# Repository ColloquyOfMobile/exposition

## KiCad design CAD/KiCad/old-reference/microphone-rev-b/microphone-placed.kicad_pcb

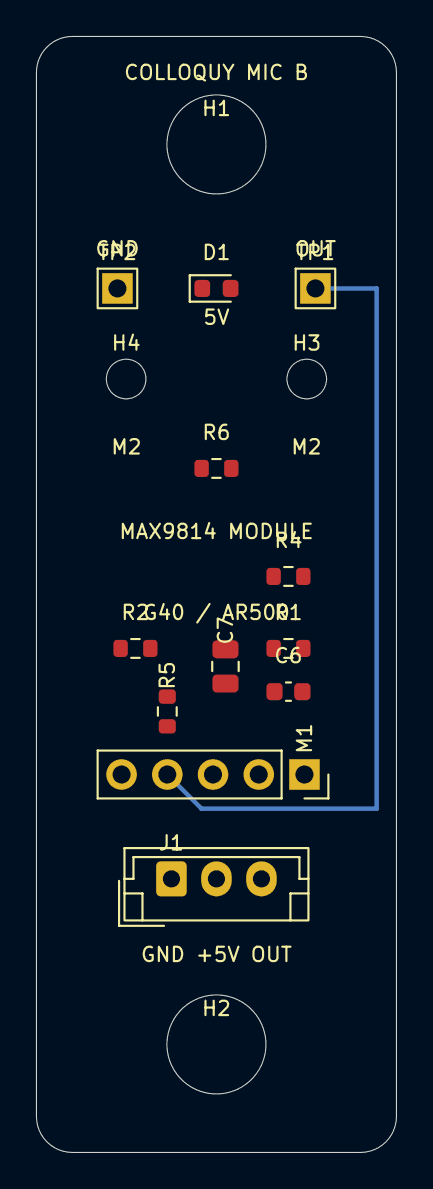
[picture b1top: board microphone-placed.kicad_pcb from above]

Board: 2 copper layers, 20.0 x 62.0 mm, 16 parts (0 on the bottom side), 8 nets.

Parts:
C6: 100nF; C_0603_1608Metric
C7: 22uF X5R 10V; C_0805_2012Metric
D1: GREEN LED; LED_0603_1608Metric
H1, H2: M5 / 12mm copper keepout; MountingHole_5.5mm_Keepout12
H3, H4: M2 MODULE / INSULATING SPACER; MountingHole_2.2mm_M2_Keepout6
J1: GND / +5V / OUT; JST_EH_B3B-EH-A_1x03_P2.50mm_Vertical
M1: MAX9814 MODULE / 1x05 SOCKET; MAX9814_Module_Socket_1x05
R1: 0R / GAIN VDD 40dB; R_0603_1608Metric
R2: 0R / AR GND 1:500; R_0603_1608Metric
R4: 33R; R_0603_1608Metric
R5: 470R; R_0603_1608Metric
R6: 2K2; R_0603_1608Metric
TP1: MICOUT; TestPin_1x01_P2.54mm
TP2: GND; TestPin_1x01_P2.54mm

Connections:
+5V: J1.2, R4.1, R6.1
AR: M1.5, R2.1
GAIN: M1.3, R1.1
GND: C6.2, C7.2, D1.1, J1.1, M1.1, R2.2, TP2.1
MICOUT: M1.4, R5.1, TP1.1
OUT: J1.3, R5.2
VDD: C6.1, C7.1, M1.2, R1.2, R4.2
led/D1: D1.2, R6.2

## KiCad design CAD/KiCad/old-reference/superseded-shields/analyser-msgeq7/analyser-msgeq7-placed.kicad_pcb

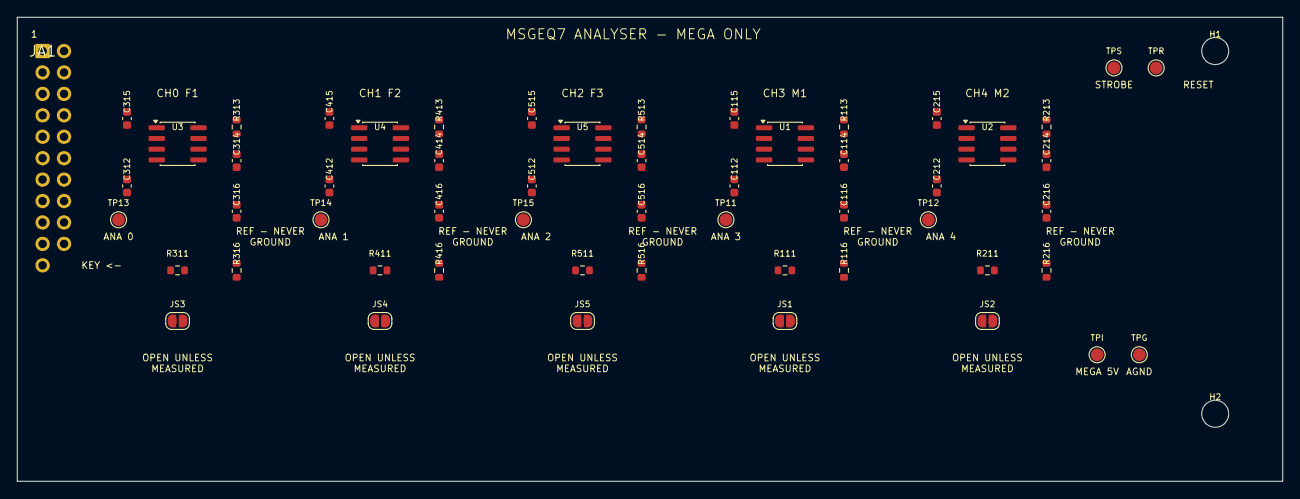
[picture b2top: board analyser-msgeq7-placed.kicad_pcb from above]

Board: 2 copper layers, 150.0 x 55.0 mm, 57 parts (1 on the bottom side), 34 nets, no tracks yet.

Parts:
C112, C115, C116, C212, C215, C216, C312, C315, C316, C412, C415, C416, C512, C515, C516: 100nF; C_0603_1608Metric
C114, C214, C314, C414, C514: 33pF C0G; C_0603_1608Metric
H1, H2: M3 retention; MountingHole_3.2mm_M3
JA1: ANALYSER - KEY 22; Socket_2x11_Key22
JS1, JS2, JS3, JS4, JS5: ATTEN BYPASS (OPEN); SolderJumper-2_P1.3mm_Open_RoundedPad1.0x1.5mm
R111, R211, R311, R411, R511: 47K; R_0603_1608Metric
R113, R213, R313, R413, R513: 200K 1%; R_0603_1608Metric
R116, R216, R316, R416, R516: 6K8; R_0603_1608Metric
TP11, TP12, TP13, TP14, TP15: test pad; TestPoint_Pad_D1.5mm
TPG: AGND; TestPoint_Pad_D1.5mm
TPI: MEGA_5V; TestPoint_Pad_D1.5mm
TPR: analyser/reset; TestPoint_Pad_D1.5mm
TPS: analyser/strobe; TestPoint_Pad_D1.5mm
U1, U2, U3, U4, U5: MSGEQ7N; SOIC-8_3.9x4.9mm_P1.27mm

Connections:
AGND: C114.2, C115.2, C116.2, C214.2, C215.2, C216.2, C314.2, C315.2, C316.2, C414.2, C415.2, C416.2, C514.2, C515.2, C516.2, JA1.2, JA1.4, JA1.6, JA1.8, JA1.10, JA1.16, R116.2, R216.2, R316.2, R416.2, R516.2, TPG.1, U1.2, U2.2, U3.2, U4.2, U5.2
MEGA_5V: C115.1, C215.1, C315.1, C415.1, C515.1, JA1.19, R113.1, R213.1, R313.1, R413.1, R513.1, TPI.1, U1.1, U2.1, U3.1, U4.1, U5.1
analyser/reset: JA1.18, TPR.1, U1.7, U2.7, U3.7, U4.7, U5.7
analyser/strobe: JA1.17, TPS.1, U1.4, U2.4, U3.4, U4.4, U5.4
female1/analyser out: JA1.11, TP13.1, U3.3
female1/internal reference: C316.1, U3.6
female1/mic attenuated: C312.1, JS3.2, R311.2, R316.1
female1/microphone: JA1.1, JS3.1, R311.1
female1/msgeq input: C312.2, U3.5
female1/oscillator: C314.1, R313.2, U3.8
female2/analyser out: JA1.12, TP14.1, U4.3
female2/internal reference: C416.1, U4.6
female2/mic attenuated: C412.1, JS4.2, R411.2, R416.1
female2/microphone: JA1.3, JS4.1, R411.1
female2/msgeq input: C412.2, U4.5
female2/oscillator: C414.1, R413.2, U4.8
female3/analyser out: JA1.13, TP15.1, U5.3
female3/internal reference: C516.1, U5.6
female3/mic attenuated: C512.1, JS5.2, R511.2, R516.1
female3/microphone: JA1.5, JS5.1, R511.1
female3/msgeq input: C512.2, U5.5
female3/oscillator: C514.1, R513.2, U5.8
male1/analyser out: JA1.14, TP11.1, U1.3
male1/internal reference: C116.1, U1.6
male1/mic attenuated: C112.1, JS1.2, R111.2, R116.1
male1/microphone: JA1.7, JS1.1, R111.1
male1/msgeq input: C112.2, U1.5
male1/oscillator: C114.1, R113.2, U1.8
male2/analyser out: JA1.15, TP12.1, U2.3
male2/internal reference: C216.1, U2.6
male2/mic attenuated: C212.1, JS2.2, R211.2, R216.1
male2/microphone: JA1.9, JS2.1, R211.1
male2/msgeq input: C212.2, U2.5
male2/oscillator: C214.1, R213.2, U2.8

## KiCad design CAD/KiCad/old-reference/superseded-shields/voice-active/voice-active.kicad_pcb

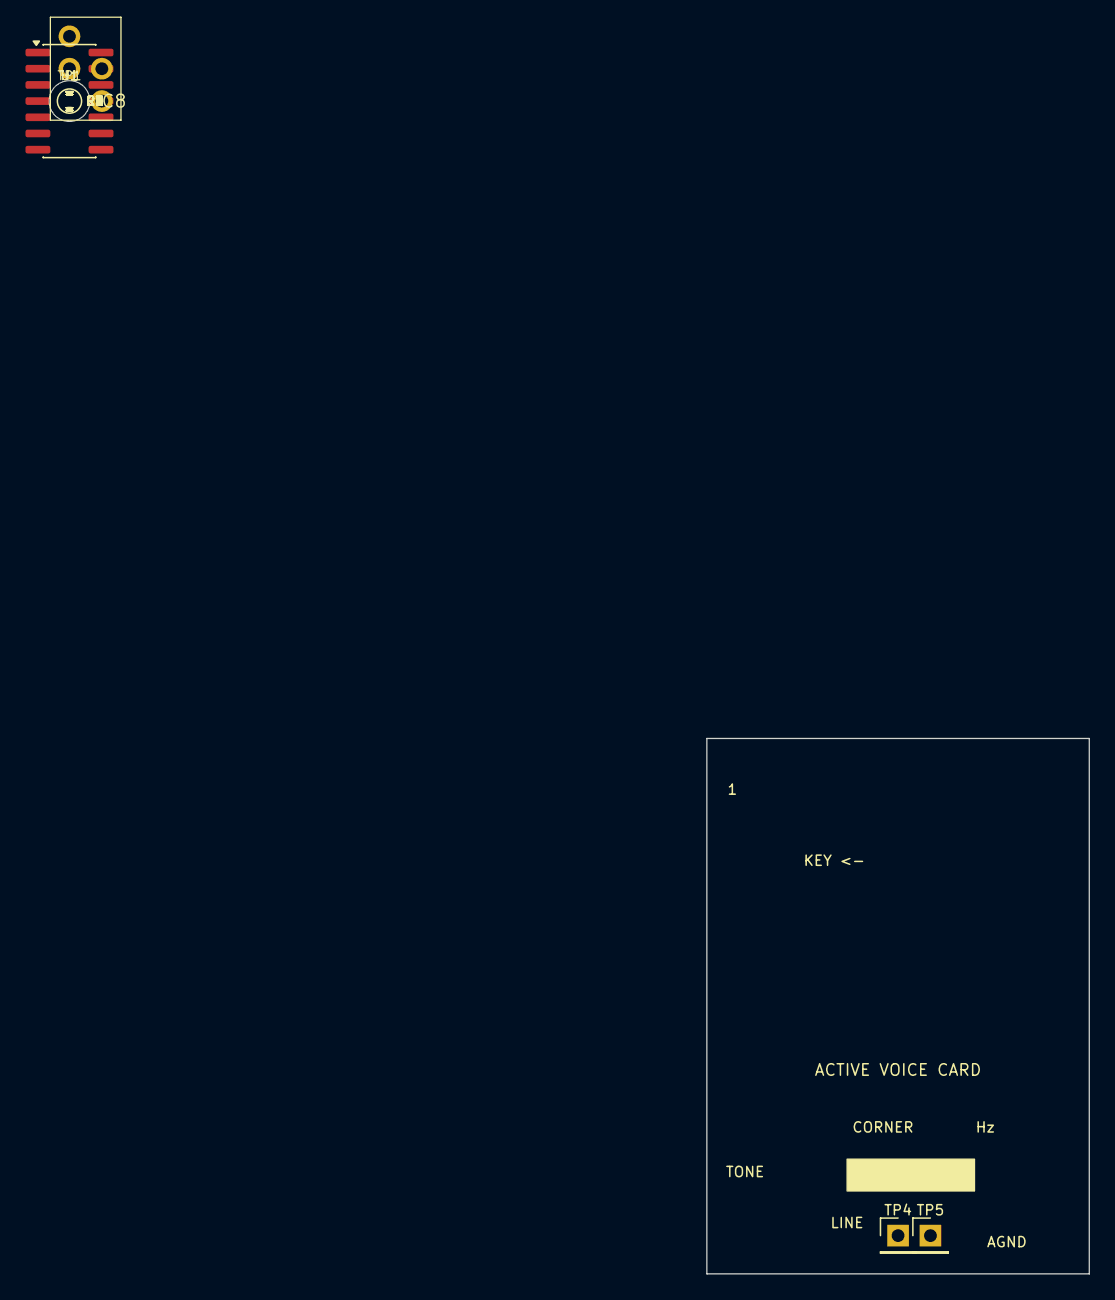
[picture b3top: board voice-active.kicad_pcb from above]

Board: 2 copper layers, 30.0 x 42.0 mm, 23 parts (0 on the bottom side), 14 nets, no tracks yet.

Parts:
C2: 12nF C0G; C_0805_2012Metric
C3: 10nF C0G; C_0805_2012Metric
C4: 22nF C0G; C_0805_2012Metric
C5: 3.3nF C0G; C_0805_2012Metric
C6, C9: 10uF X7R; C_0805_2012Metric
C7: 1uF X7R; C_0805_2012Metric
C8: 100nF; C_0603_1608Metric
H1: M3 retention; MountingHole_3.2mm_M3
JV1: VOICE - KEY 6; Socket_2x03_Key6
R1: 15K; R_0603_1608Metric
R2, R7, R8: 10K; R_0603_1608Metric
R3, R4: 10K2; R_0603_1608Metric
R5, R6: 13K3; R_0603_1608Metric
R9: 100K; R_0603_1608Metric
TP1: tone; TestPoint_Pad_D1.5mm
TP4: filter out; TestPin_1x01_P2.54mm
TP5: AGND; TestPin_1x01_P2.54mm
U1: MCP6024-I/SL; SOIC-14_3.9x8.7mm_P1.27mm

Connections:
+5V: C8.1, C9.1, JV1.5, R7.1, U1.4
AGND: C3.2, C5.2, C6.2, C8.2, C9.2, JV1.4, R8.2, R9.2, TP5.1, U1.11
buffer: R3.1, U1.1, U1.2
filter out: C7.2, JV1.3, R9.1, TP4.1
input: R1.2, R2.1, U1.3
ref/raw: C6.1, R7.2, R8.1, U1.12
stage1/in: C3.1, R4.2, U1.5
stage1/mid: C2.1, R3.2, R4.1
stage1/out: C2.2, R5.1, U1.6, U1.7
stage2/in: C5.1, R6.2, U1.10
stage2/mid: C4.1, R5.2, R6.1
stage2/out: C4.2, C7.1, U1.8, U1.9
tone: JV1.1, R1.1, TP1.1
vref: R2.2, U1.13, U1.14

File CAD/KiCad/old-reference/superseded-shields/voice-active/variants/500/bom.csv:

Reference,Value,Footprint,MPN,Assembly
JV1,VOICE - KEY 6,Shields:Socket_2x03_Key6,,fit
R1,15K,Shields:R_0603_1608Metric,,fit
R2,10K,Shields:R_0603_1608Metric,,fit
U1,MCP6024-I/SL,Shields:SOIC-14_3.9x8.7mm_P1.27mm,MCP6024-I/SL,fit
R3,29400 ohm 1%,Shields:R_0603_1608Metric,,fit
R4,29400 ohm 1%,Shields:R_0603_1608Metric,,fit
C2,12nF C0G,Shields:C_0805_2012Metric,,fit
C3,10nF C0G,Shields:C_0805_2012Metric,,fit
R5,37400 ohm 1%,Shields:R_0603_1608Metric,,fit
R6,37400 ohm 1%,Shields:R_0603_1608Metric,,fit
C4,22nF C0G,Shields:C_0805_2012Metric,,fit
C5,3.3nF C0G,Shields:C_0805_2012Metric,,fit
R7,10K,Shields:R_0603_1608Metric,,fit
R8,10K,Shields:R_0603_1608Metric,,fit
C6,10uF X7R,Shields:C_0805_2012Metric,,fit
C7,1uF X7R,Shields:C_0805_2012Metric,,fit
R9,100K,Shields:R_0603_1608Metric,,fit
C8,100nF,Shields:C_0603_1608Metric,,fit
C9,10uF X7R,Shields:C_0805_2012Metric,,fit

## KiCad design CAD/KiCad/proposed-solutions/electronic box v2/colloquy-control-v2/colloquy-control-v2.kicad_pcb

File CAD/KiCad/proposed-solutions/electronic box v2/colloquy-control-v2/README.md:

# Colloquy control PCB v2 — revision A prototype

Open **`colloquy-control-v2.kicad_pro` in KiCad 9**. The project contains the
complete schematic and routed replacement for the electronic-box board. Its
fixed harness and firmware-4 interfaces come from `../NETLIST.md` and
`Source code/Python/colloquy/hardware/electronics/NEXT_PCB.md`.

## Files and editing

- `colloquy-control-v2.kicad_sch`: overview with controller, power, harness,
  I/O, and five audio channel sheets.
- `colloquy-control-v2.kicad_pcb`: canonical board to edit and manufacture.
- `Colloquy.kicad_sym`, `Colloquy.pretty/`, and library tables: local design
  libraries, including recovered custom footprints.
- `circuit.json`: explicit pin-to-net design contract; `footprint-map.json`
  relates upstream identifiers to the local footprints.
- `reports/`: electrical checks, board checks, and inspection exports.
- `manufacturing/`: prototype fabrication and assembly outputs.

`manufacturing/ASSEMBLY_NOTES.md` lists sockets, mating headers, and mounting
hardware in addition to the electrical BOM. It explains the inherited Mega
footprint's position-file convention and the solid ground-pad connections.

Edit the native KiCad files normally. The scripts in `scripts/` are optional
regeneration tools; they do not observe subsequent manual edits. In particular,
`build_schematic.py` regenerates the sheets and circuit contract, while
`build_board.py` produces a separate `-placed.kicad_pcb`. Never overwrite a
manually edited or routed design unintentionally. The repository-root
`next_pcb.py` still generates the older, incomplete planning netlist one
directory above; it does not regenerate this completed project.

## Chosen construction

Two copper layers, nominal 1.6 mm FR-4, 35 µm finished copper per side,
lead-free finish, solder mask both sides, and component legends. Outline:
210 × 297 mm with 5 mm corner radii. Existing connectors, Mega shield, and
U2D2 locations remain fixed. The Mega plugs into the **bottom** of the PCB.

Four additional 3.2 mm M3 standoff holes have 8 mm copper keepouts. Four
existing U2D2 apertures become 4.5 mm NPTH drills; the jack locating aperture
becomes a 1.6 mm NPTH drill. There are no additional large cutouts. See
`../MECHANICAL_REVIEW.md` for coordinates and the dry-fit checks.

Nominal routing: 0.30 mm signals, 0.50 mm analogue supplies/ground,
2.00 mm body-power trunks; 0.25 mm clearance. Standard vias are 0.80/0.40 mm
diameter/drill, with 1.20/0.60 mm vias for body power. The board and Mega
5 V rails remain separate. JP1 is the sole on-board AGND–GND bond.

## Assembly and commissioning

This is a **prototype design**, not a measured replacement-board qualification.
Read `CIRCUIT_NOTES.md` for receiver changes and assembly options. Fit MSGEQ7P
DIP-8 devices in sockets, 1% resistors, and C0G/NP0 33 pF oscillator capacitors.
Use at least 16 V-rated supply capacitors; select filter capacitors with the
stated values, appropriate lead pitch, and preferably 5% tolerance.

1. Print the mechanical drawing at 1:1 and dry-fit the enclosure, connectors,
   Mega underside clearance, U2D2, and new standoffs.
2. Check continuity, polarity, and isolation between BOARD +5V and MEGA_5V.
   Bring up with current-limited supplies before connecting the harness.
3. Measure the provisional 10 kΩ photosensor loads against the installed
   sensors; replace their values where calibration requires it.
4. Verify all five filter outputs and analyser bands using firmware 4. Leave
   microphone attenuation bypasses open until measured headroom permits them.
5. Test a full-length body cable with NeoPixels and servos active. Confirm rail
   voltage drop and connector temperature under the actual load. Initially
   limit each external rail to 2 A total and each powered DSUB branch to 1 A;
   these are commissioning ceilings, not established hardware ratings.

The body amplifiers are external to this PCB. Their supply voltage must follow
the selected module's actual rating; the previously damaged GF1002 is not
assumed to accept 12 V. This design preserves both existing harness rails.

## Reproducibility and library provenance

Use KiCad's bundled Python for PCB scripts because it includes `pcbnew`.
Run `export_release.py` with an ordinary Python installation; the Windows
KiCad-bundled interpreter can cause its CLI child process to fail at startup.
Routing uses Freerouting 2.4.1 with a separately supplied Java 25 runtime; the
script runs locally with network services and analytics disabled. It preserves
the placed input and requires a different output filename. DRC and exported
netlist comparison must be repeated after design edits.

`scripts/export_release.py` runs ERC, DRC, native schematic/PCB parity, and
the explicit circuit-contract comparison before generating fabrication files.
Any reported error or warning stops export. It also verifies all nine NPTH
drill hits by diameter and coordinate. Use the generated Gerber ZIP for the
fabricator; its contents come exclusively from that export run. Release hashes
cover every schematic sheet, the board, project settings, and local libraries.

Standard footprints derive from the KiCad 9 library, maintained by the KiCad
community under [CC-BY-SA 4.0 with the KiCad exception](https://www.kicad.org/libraries/license/).
Custom jack, bridge, U2D2, and Mega geometry derives from the existing project;
the source identifiers are retained in `circuit.json`. The jack retention pads
have enlarged annular rings, and round mechanical apertures were converted to
NPTH pads. Standard 3D models use KiCad's optional model installation. Custom
device 3D bodies are absent; the 3D view does not establish enclosure fit.

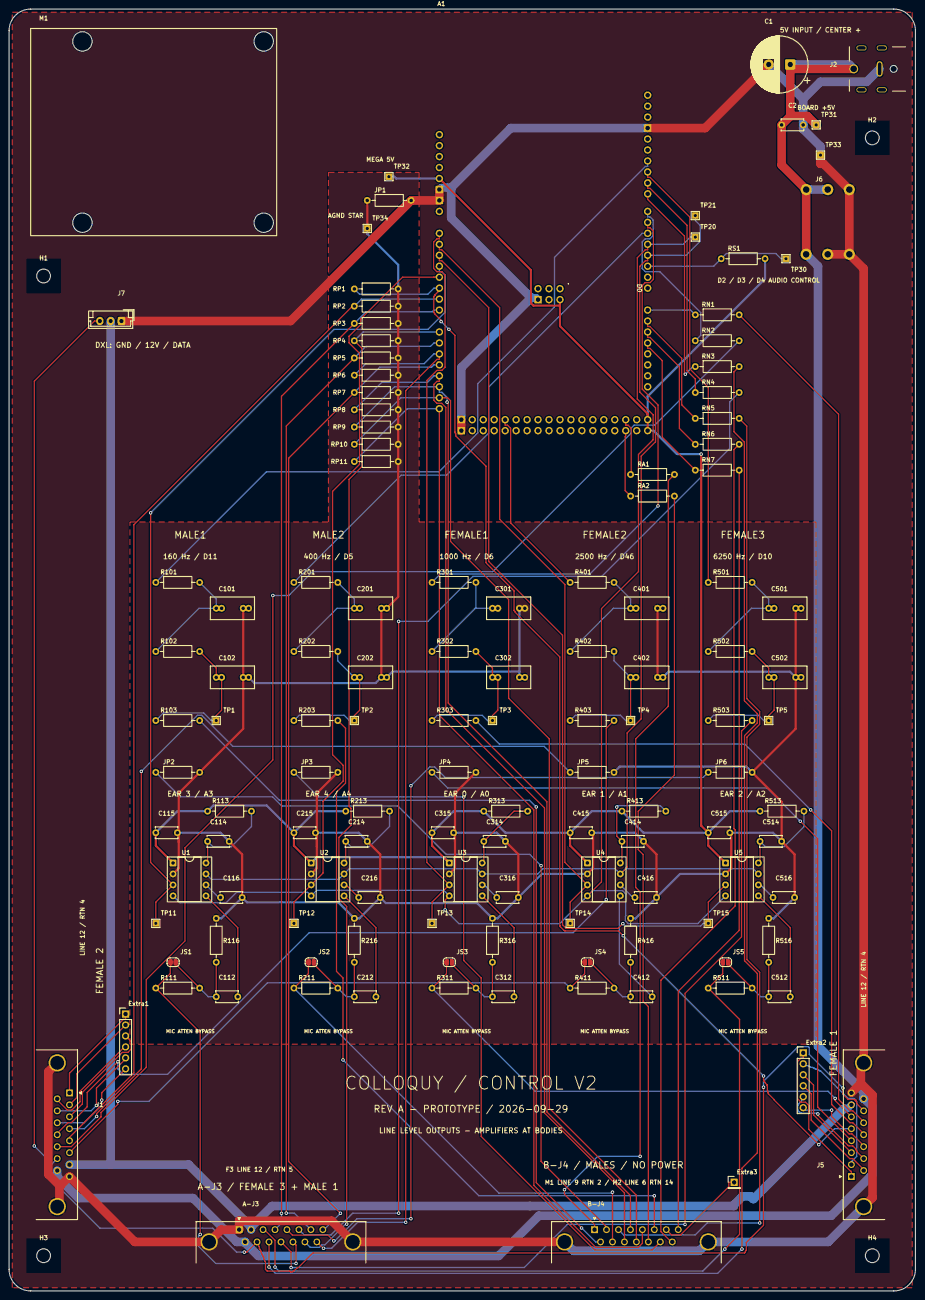
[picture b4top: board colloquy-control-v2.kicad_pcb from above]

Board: 2 copper layers, 210.0 x 297.0 mm, 132 parts (0 on the bottom side), 106 nets.

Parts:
A1: Arduino Mega 2560; Arduino_Mega2560_R3_Shield
A-J3: DSUB-15; DSUB-15_Pins_Horizontal_P2.77x2.84mm_EdgePinOffset4.94mm_Ho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
B-J4: DSUB-15; DSUB-15_Pins_Horizontal_P2.77x2.84mm_EdgePinOffset4.94mm_Ho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
C1: 470uF 16V; CP_Radial_D13.0mm_P5.00mm
C2, C112, C115, C116, C212, C215, C216, C312, C315, C316, C412, C415, C416, C512, C515, C516: 100nF; C_Disc_D5.0mm_W2.5mm_P5.00mm
C101, C102: 470nF; C_Rect_L10.0mm_W5.0mm_P5.00mm_P7.50mm
C114, C214, C314, C414, C514: 33pF C0G; C_Disc_D5.0mm_W2.5mm_P5.00mm
C201, C202: 220nF; C_Rect_L10.0mm_W5.0mm_P5.00mm_P7.50mm
C301, C302: 150nF; C_Rect_L10.0mm_W5.0mm_P5.00mm_P7.50mm
C401, C402: 47nF; C_Rect_L10.0mm_W5.0mm_P5.00mm_P7.50mm
C501, C502: 10nF; C_Rect_L10.0mm_W5.0mm_P5.00mm_P7.50mm
Extra1, Extra2: 1x6 header; PinHeader_1x06_P2.54mm_Vertical
Extra3: 1x1 pad; PinHeader_1x01_P2.54mm_Vertical
H1, H2, H3, H4: M3 3.2mm NPTH; MountingHole_3.2mm_M3
J1, J5: DSUB-15; DSUB-15_Pins_Horizontal_P2.77x2.84mm_EdgePinOffset4.94mm_Ho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
J2: DC jack; PJ-082BH_jack_10A
J6: screw bridge; screw_brigde
J7: JST EH 3; JST_EH_B3B-EH-A_1x03_P2.50mm_Vertical
JP1, JP2, JP3, JP4, JP5, JP6: 0R; R_Axial_DIN0207_L6.3mm_D2.5mm_P10.16mm_Horizontal
JS1, JS2, JS3, JS4, JS5: ATTEN BYPASS (OPEN); SolderJumper-2_P1.3mm_Open_RoundedPad1.0x1.5mm
M1: U2D2; u2d2_mounting
R101, R102, R501, R502: 2K2; R_Axial_DIN0207_L6.3mm_D2.5mm_P10.16mm_Horizontal
R103, R203, R303, R403, R503: 100R; R_Axial_DIN0207_L6.3mm_D2.5mm_P10.16mm_Horizontal
R111, R211, R311, R411, R511: 47K; R_Axial_DIN0207_L6.3mm_D2.5mm_P10.16mm_Horizontal
R113, R213, R313, R413, R513: 200K 1%; R_Axial_DIN0207_L6.3mm_D2.5mm_P10.16mm_Horizontal
R116, R216, R316, R416, R516: 6K8; R_Axial_DIN0207_L6.3mm_D2.5mm_P10.16mm_Horizontal
R201, R202: 2K; R_Axial_DIN0207_L6.3mm_D2.5mm_P10.16mm_Horizontal
R301, R302: 1K2; R_Axial_DIN0207_L6.3mm_D2.5mm_P10.16mm_Horizontal
R401, R402: 1K8; R_Axial_DIN0207_L6.3mm_D2.5mm_P10.16mm_Horizontal
RA1, RA2: 330R; R_Axial_DIN0207_L6.3mm_D2.5mm_P10.16mm_Horizontal
RN1, RN2, RN3, RN4, RN5, RN6, RN7: 330R; R_Axial_DIN0207_L6.3mm_D2.5mm_P10.16mm_Horizontal
RP1, RP2, RP3, RP4, RP5, RP6, RP7, RP8, RP9, RP10, RP11: 10K provisional; R_Axial_DIN0207_L6.3mm_D2.5mm_P10.16mm_Horizontal
RS1: 10K; R_Axial_DIN0207_L6.3mm_D2.5mm_P10.16mm_Horizontal
TP1, TP2, TP3, TP4, TP5, TP11, TP12, TP13, TP14, TP15, TP20, TP21, TP30, TP31, TP32, TP33, TP34: test pad; TestPoint_THTPad_1.5x1.5mm_Drill0.7mm
U1, U2, U3, U4, U5: MSGEQ7; DIP-8_W7.62mm_Socket

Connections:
+5V: A-J3.9, C1.1, C2.1, J1.15, J2.1, J5.15, J6.3, J6.5, J6.6, TP31.1
+12V: A-J3.2, J1.7, J5.7, J7.2
AGND: C101.2, C102.2, C114.2, C115.2, C116.2, C201.2, C202.2, C214.2, C215.2, C216.2, C301.2, C302.2, C314.2, C315.2, C316.2, C401.2, C402.2, C414.2, C415.2, C416.2, C501.2, C502.2, C514.2, C515.2, C516.2, JP1.1, JP2.2, JP3.2, JP4.2, JP5.2, JP6.2, R116.2, R216.2, R316.2, R416.2, R516.2, RP1.2, RP2.2, RP3.2, RP4.2, RP5.2, RP6.2, RP7.2, RP8.2, RP9.2, RP10.2, RP11.2, TP34.1, U1.2, U2.2, U3.2, U4.2, U5.2
GND: A1.GND1 (GND), A1.GND2 (GND), A1.GND3 (GND), A1.GND4 (SPI_GND), A1.GND5 (GND), A1.GND6 (GND), A-J3.0, A-J3.1, B-J4.0, C1.2, C2.2, J1.0, J1.8, J2.2, J5.0, J5.8, J6.1, J6.2, J6.4, J7.1, JP1.2, TP33.1
MEGA_5V: A1.5V1 (5V), A1.5V2 (SPI_5V), A1.5V3 (5V), A1.5V4 (5V), C115.1, C215.1, C315.1, C415.1, C515.1, R113.1, R213.1, R313.1, R413.1, R513.1, RS1.2, TP32.1, U1.1, U2.1, U3.1, U4.1, U5.1
amp shutdown: A1.D2 (D2_INT0), RS1.1, TP30.1
analyser/reset: A1.D3 (D3_INT1), TP21.1, U1.7, U2.7, U3.7, U4.7, U5.7
analyser/strobe: A1.D4, TP20.1, U1.4, U2.4, U3.4, U4.4, U5.4
centre/spare1: B-J4.7, Extra3.1
dxl_data: A-J3.10, J1.14, J5.14, J7.3
female1/analyser out: A1.A0, TP13.1, U3.3
female1/audio return: J5.4, JP4.1
female1/filter mid: C301.1, R301.2, R302.1
female1/filter out: C302.1, R302.2, R303.1, TP3.1
female1/internal reference: C316.1, U3.6
female1/line out: J5.12, R303.2
female1/mic attenuated: C312.1, JS3.2, R311.2, R316.1
female1/microphone: J5.6, JS3.1, R311.1
female1/msgeq input: C312.2, U3.5
female1/neopixel: J5.13, RN1.2
female1/neopixel/driven: A1.D14 (D14/TX3), RN1.1
female1/oscillator: C314.1, R313.2, U3.8
female1/photosensor: A1.A5, J5.5, RP1.1
female1/spare1: Extra2.1, J5.1
female1/spare2: Extra2.2, J5.2
female1/spare3: Extra2.3, J5.3
female1/spare4: Extra2.4, J5.9
female1/spare5: Extra2.5, J5.10
female1/spare6: Extra2.6, J5.11
female1/tone: A1.D6, R301.1
female2/analyser out: A1.A1, TP14.1, U4.3
female2/audio return: J1.4, JP5.1
female2/filter mid: C401.1, R401.2, R402.1
female2/filter out: C402.1, R402.2, R403.1, TP4.1
female2/internal reference: C416.1, U4.6
female2/line out: J1.12, R403.2
female2/mic attenuated: C412.1, JS4.2, R411.2, R416.1
female2/microphone: J1.6, JS4.1, R411.1
female2/msgeq input: C412.2, U4.5
female2/neopixel: J1.13, RN2.2
female2/neopixel/driven: A1.D7, RN2.1
female2/oscillator: C414.1, R413.2, U4.8
female2/photosensor: A1.A6, J1.5, RP2.1
female2/spare1: Extra1.1, J1.1
female2/spare2: Extra1.2, J1.2
female2/spare3: Extra1.3, J1.3
female2/spare4: Extra1.4, J1.9
female2/spare5: Extra1.5, J1.10
female2/spare6: Extra1.6, J1.11
female2/tone: A1.D46, R401.1
female3/analyser out: A1.A2, TP15.1, U5.3
female3/audio return: A-J3.5, JP6.1
female3/filter mid: C501.1, R501.2, R502.1
female3/filter out: C502.1, R502.2, R503.1, TP5.1
female3/internal reference: C516.1, U5.6
female3/line out: A-J3.12, R503.2
female3/mic attenuated: C512.1, JS5.2, R511.2, R516.1
female3/microphone: A-J3.3, JS5.1, R511.1
female3/msgeq input: C512.2, U5.5
female3/neopixel: A-J3.11, RN3.2
female3/neopixel/driven: A1.D8, RN3.1
female3/oscillator: C514.1, R513.2, U5.8
female3/photosensor: A1.A7, A-J3.4, RP3.1
female3/tone: A1.D10, R501.1
male1/analyser out: A1.A3, TP11.1, U1.3
male1/audio return: B-J4.2, JP2.1
male1/aux: B-J4.1, RA1.2
male1/aux driven: A1.D24, RA1.1
male1/bar neopixel: B-J4.15, RN6.2
male1/bar neopixel/driven: A1.D16 (D16/TX2), RN6.1
male1/filter mid: C101.1, R101.2, R102.1
male1/filter out: C102.1, R102.2, R103.1, TP1.1
male1/internal reference: C116.1, U1.6
male1/line out: B-J4.9, R103.2
male1/mic attenuated: C112.1, JS1.2, R111.2, R116.1
male1/microphone: A-J3.13, JS1.1, R111.1
male1/msgeq input: C112.2, U1.5
male1/neopixel: A-J3.6, RN4.2
male1/neopixel/driven: A1.D9, RN4.1
male1/oscillator: C114.1, R113.2, U1.8
male1/photosensor/A: A1.A8, A-J3.14, RP4.1
male1/photosensor/B: A1.A9, A-J3.7, RP5.1
male1/photosensor/C: A1.A10, A-J3.15, RP6.1
male1/photosensor/D: A1.A11, A-J3.8, RP7.1
male1/tone: A1.D11, R101.1
male2/analyser out: A1.A4, TP12.1, U2.3
male2/audio return: B-J4.14, JP3.1
male2/aux: B-J4.13, RA2.2
male2/aux driven: A1.D25, RA2.1
male2/bar neopixel: B-J4.8, RN7.2
male2/bar neopixel/driven: A1.D17 (D17/RX2), RN7.1
male2/filter mid: C201.1, R201.2, R202.1
male2/filter out: C202.1, R202.2, R203.1, TP2.1
male2/internal reference: C216.1, U2.6
male2/line out: B-J4.6, R203.2
male2/mic attenuated: C212.1, JS2.2, R211.2, R216.1
male2/microphone: B-J4.10, JS2.1, R211.1
male2/msgeq input: C212.2, U2.5
male2/neopixel: B-J4.3, RN5.2
male2/neopixel/driven: A1.D15 (D15/RX3), RN5.1
male2/oscillator: C214.1, R213.2, U2.8
male2/photosensor/A: A1.A12, B-J4.11, RP8.1
male2/photosensor/B: A1.A13, B-J4.4, RP9.1
male2/photosensor/C: A1.A14, B-J4.12, RP10.1
male2/photosensor/D: A1.A15, B-J4.5, RP11.1
male2/tone: A1.D5, R201.1

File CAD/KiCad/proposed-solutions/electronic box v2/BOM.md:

# The next PCB — bill of materials

**Generated. Do not edit.** Run `py next_pcb.py` from the repo root after changing `colloquy/hardware/electronics/next_pcb.py`.

## Decided

| Kind | Value | Qty | References |
|---|---|---|---|
| analyser | **MSGEQ7** | 5 | U1, U2, U3, U4, U5 |
| board | **Arduino Mega 2560** | 1 | A1 |
| board | **U2D2** | 1 | M1 |
| capacitor | **100nF** | 1 | C2 |
| capacitor | **10nF** | 2 | C501, C502 |
| capacitor | **150nF** | 2 | C301, C302 |
| capacitor | **220nF** | 2 | C201, C202 |
| capacitor | **470nF** | 2 | C101, C102 |
| capacitor | **470uF** | 1 | C1 |
| capacitor | **47nF** | 2 | C401, C402 |
| connector | **1x1 pad** | 1 | Extra3 |
| connector | **1x6 header** | 2 | Extra1, Extra2 |
| connector | **DC jack** | 1 | J2 |
| connector | **DSUB-15** | 4 | A-J3, B-J4, J1, J5 |
| connector | **JST EH 3** | 1 | J7 |
| connector | **screw bridge** | 1 | J6 |
| link | **0R** | 6 | JP1, JP2, JP3, JP4, JP5, JP6 |
| resistor | **100R** | 5 | R103, R203, R303, R403, R503 |
| resistor | **10K** | 1 | RS1 |
| resistor | **1K2** | 2 | R301, R302 |
| resistor | **1K8** | 2 | R401, R402 |
| resistor | **2K** | 2 | R201, R202 |
| resistor | **2K2** | 4 | R101, R102, R501, R502 |
| resistor | **330R** | 9 | RA1, RA2, RN1, RN2, RN3, RN4, RN5, RN6, RN7 |
| test point | **test pad** | 17 | TP1, TP11, TP12, TP13, TP14, TP15, TP2, TP20, TP21, TP3, TP30, TP31, TP32, TP33, TP34, TP4, TP5 |

---

## Not decided here — confirm before ordering

Neither group below is recorded in this repository, and neither is
the generator's to invent. They are kept apart rather than mixed in
above, because a plausible-looking number passing for a known one is
exactly how a board comes back wrong.

- **The MSGEQ7 support network.** The analyser array is five
  ready-made modules today (`HARDWARE_SETUP.md` section 4) and
  nobody here has drawn the chip. The values below are its
  datasheet's typical application, carried so the schematic has
  something to place. Read them off the datasheet before ordering,
  and take the pin numbering from it too — this netlist names the
  chip's terminals rather than numbering them, on purpose.
- **The light-sensor dividers.** `as built` records that the KiCad
  files do not say whether what sits across `J11`/`J12` is a shunt
  or a resistor, and that the light sensors work, so it is
  something. Measure one and put the number here.

| Kind | Value | Qty | References |
|---|---|---|---|
| capacitor | **100nF** | 5 | C115, C215, C315, C415, C515 |
| capacitor | **10nF** | 5 | C112, C212, C312, C412, C512 |
| capacitor | **33pF** | 5 | C114, C214, C314, C414, C514 |
| resistor | **200K** | 5 | R113, R213, R313, R413, R513 |
| resistor | **22K** | 5 | R111, R211, R311, R411, R511 |
| resistor | **TBC** | 11 | RP1, RP10, RP11, RP2, RP3, RP4, RP5, RP6, RP7, RP8, RP9 |

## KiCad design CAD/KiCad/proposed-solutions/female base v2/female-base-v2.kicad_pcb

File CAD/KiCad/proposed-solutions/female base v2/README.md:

# Female base v2 - socketed GF1002 amplifier

Open `female-base-v2.kicad_pro` in KiCad 9. The routed board, main schematic,
continuous-wire schematic, BOM, STEP model, previews, Gerbers and reports follow
the user's **2026-10-21 placement**. The original `../female base/` is preserved.

## Current layout

The authoritative placement checkpoint is `female-base-v2-placed.kicad_pcb`.
The routed `female-base-v2.kicad_pcb` retains all its component positions and
orientations. The user moved four components and removed H1/H2, the two M2
amplifier-support mounting holes. H1/H2 are also removed from both schematics
and the circuit metadata. No replacement support holes were added. The original
artwork outline, cutouts, DSUB geometry and harness pin assignments are retained.

| Part | X (mm) | Y (mm) | Rotation |
|---|---:|---:|---:|
| R1, 22K | 39.545 | 57.390 | 0 degrees |
| R2, 3K3 | 41.345 | 59.930 | 0 degrees |
| C1, 220 uF / 10 V SMD | 33.890 | 46.980 | 180 degrees |
| C2, 100 nF / 0603 | 34.085 | 67.610 | 180 degrees |

The remaining connector and socket positions are unchanged. Every connector
has a front silkscreen name: J2 DXL MIRROR, J3 MICROPHONE, J4 PHOTOSENSOR,
J5 NEOPIXEL, J6 SPEAKER and J7 HARNESS. See
[`reports/connector-names.png`](<reports/connector-names.png>).

The [continuous-wire schematic](<wired/female-base-v2-wired.pdf>) is an editable
KiCad reading copy in `wired/`. Its existing layout is preserved. Both schematic
copies contain 11 components and agree on 38 connected pins and 12 electrical
nets. [The comparison](<wired/comparison.md>) explains the additions relative to
the original female base.

## Audio and power

The module itself mounts on this PCB; Thomas's green perfboard, its JST sockets
and blue terminal are absent. R1 = 22K and R2 = 3K3 reproduce Thomas's input
divider. R2's bottom and module input G use AUDIO_RETURN. Module supply minus
uses GND; these are separate PCB nets.

| J7 pin | v2 function |
|---|---|
| 12 | LINE_IN, formerly remote amplifier speaker + |
| 4 | AUDIO_RETURN, formerly remote amplifier speaker - |
| 15 | 5 V supply, unchanged |
| 8 and shell pad 0 | Supply GND, unchanged |

**Disconnect the old rack class-D speaker output from J7.12/J7.4 before using
this board.** The rack must send line-level audio and its return on that pair.
J6 now connects only to the local GF1002 right-channel output.

C1 is a polarized SMD aluminium electrolytic,
`Capacitor_SMD:CP_Elec_6.3x5.8`, with a nominal 6.3 x 5.8 mm case. Pad 1 is
positive / 5 V; pad 2 is GND. The footprint is now rotated 180 degrees.
An example part is
[Panasonic EEEFN1A221UP](https://industrial.panasonic.com/ww/products/pt/aluminum-cap-smd/models/EEEFN1A221UP).
Match the purchased part's land pattern and assembly requirements. C1's 220 uF
value remains provisional. C2 is 100 nF in 0603. The amplifier branch is on
5 V only; the existing 12 V net serves the servo.

### Placement tradeoffs to verify on the bench

The capacitor positions have been preserved as requested. C2's two pads are
approximately 14.7 and 16.3 mm from the corresponding module supply contacts,
outside the previous less-than-5-mm target. C1's positive pad is about 23.3 mm
from module supply +, outside the previous less-than-9-mm target. These distances
are explicitly reported as unmet proximity targets, not as passing decoupling
checks. Check rail sag, clipping and noise with the actual module, speaker and
harness. CAD continuity does not establish electrical performance.

## Revision D plug-in module interface

The socket/header arrangement introduced on 2026-10-19 remains unchanged.
M1 is a vertical 1 x 11 female socket at 2.54 mm pitch, on the module contact
row. Socket pin 1 is at (49.55, 56.2) mm; pin n is at Y = 56.2 + 2.54*(n-1).
The contact row is based on `../provided-elements/gf1002-reference/`.

| M1 pin | Module contact | Net |
|---:|---|---|
| 1 | input R | AMP_INPUT |
| 2 | input G | AUDIO_RETURN |
| 3 | input L | no connection |
| 4 | no contact | no connection |
| 5 | power + | 5V |
| 6 | power - | GND |
| 7 | no contact | no connection |
| 8, 9 | LOUT pair | no connection |
| 10, 11 | ROUT pair | AMP_OUT_P, AMP_OUT_N to J6 |

Pin 10 = ROUT+ and pin 11 = ROUT- remain provisional: read the real module's
markings before ordering. Neither speaker output is ever connected to ground.
Confirm that input G and power minus are bonded inside the module as expected.
No PCB jumper assumes that bond.

The module uses male headers at positions 1-3, 5-6 and 8-11, plugged into the
female socket. Solder all eleven socket pins for strength. The nominal 8.5 mm
socket plus 2.5 mm header plastic puts the module underside about 11 mm above
the PCB and the pot about 28 mm high. Its shaft overhang is approximately
16 mm beyond the board's left edge. Measure actual parts and installed-body
clearances. H1/H2 are absent in this female revision; do not use the former
two-support assembly instructions for it. The final physical support arrangement
is not validated by the CAD checks.

## Routing and validation

Speaker outputs remain a short front-copper pair using 0.8 mm tracks; their
lengths are 18.153 and 19.191 mm. The input and audio return approach together
on back copper. The relocated divider's complete AMP_INPUT route is 12.275 mm;
the revised CAD length budget is 16 mm, compared with 8 mm for the old placement.
An explicit grounded front guard and local ground pours separate the output
region from the input and sensors. Checks find no parallel sensitive runs
within 2.5 mm of the outputs and no output/sensitive crossings in projection.
AUDIO_RETURN remains separate from the GND pours.

Native ERC, DRC, unconnected items and schematic/PCB parity are all zero.
`reports/validation.json` records source hashes, actual positions, routing,
removed supports and the unmet capacitor proximity targets. Simulation and CAD
checks do not establish physical fit, current capacity or noise performance.

## Rebuild and exports

To reroute from the saved placement, without rebuilding or moving components:

```powershell
& 'C:/Program Files/KiCad/9.0/bin/python.exe' 'CAD/KiCad/proposed-solutions/female base v2/scripts/route_boards.py' --only female-base-v2
& 'C:/Program Files/KiCad/9.0/bin/python.exe' 'CAD/KiCad/proposed-solutions/female base v2/scripts/finish_boards.py' --only female-base-v2
& './CAD/KiCad/proposed-solutions/female base v2/scripts/export_boards.ps1' -Only female-base-v2
& 'C:/Program Files/KiCad/9.0/bin/python.exe' 'CAD/KiCad/proposed-solutions/female base v2/scripts/verify_boards.py' --only female-base-v2
& 'C:/Program Files/KiCad/9.0/bin/python.exe' 'CAD/KiCad/proposed-solutions/female base v2/scripts/verify_wired_schematic.py'
```

The full `build_boards.py` also records these female coordinates and omits
H1/H2. It regenerates both body projects, whereas the commands above target
only the female board. Gerbers are regenerated with `export_gerbers.py` after
DRC passes. The revised package is still an engineering prototype, not a
physically qualified production release.

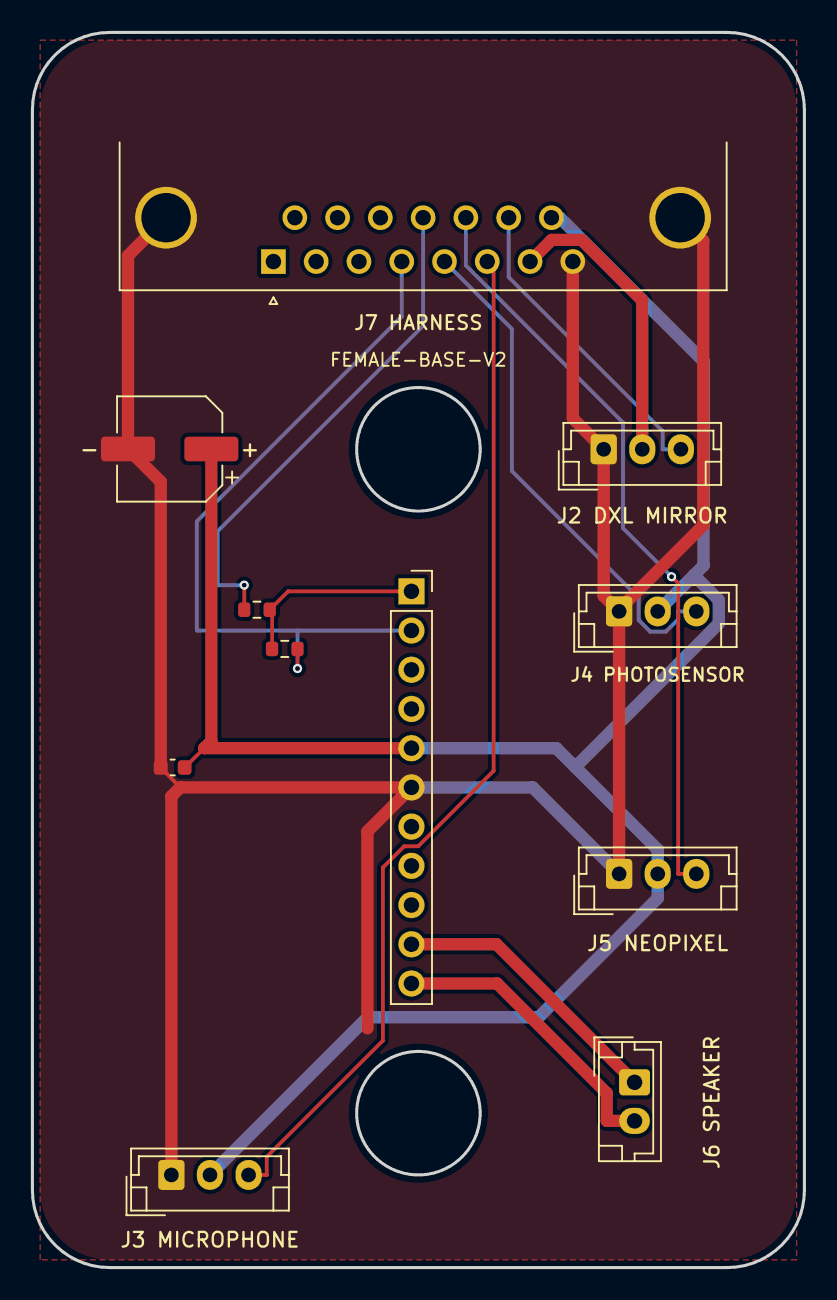
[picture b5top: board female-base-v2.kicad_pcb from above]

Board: 2 copper layers, 50.0 x 80.0 mm, 11 parts (0 on the bottom side), 12 nets.

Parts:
C1: 220uF 10V / provisional; CP_Elec_6.3x5.8
C2: 100nF; C_0603_1608Metric
J2: dxl mirror; J2_original
J3: microphone; J3_original
J4: photosensor; J4_original
J5: neopixel; J5_original
J6: Speaker; J6_original
J7: DA15_Plug_MountingHoles; J7_original
M1: GF1002 / 1x11 female socket; GF1002_PlugIn_1x11
R1: 22K; R_0603_1608Metric
R2: 3K3; R_0603_1608Metric

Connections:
5V: C1.1, C2.1, J3.2, J4.2, J5.2, J7.15, M1.5
12V: J2.2, J7.7
AMP_INPUT: M1.1, R1.2, R2.1
AMP_OUT_N: J6.2, M1.11
AMP_OUT_P: J6.1, M1.10
AUDIO_RETURN: J7.4, M1.2, R2.2
GND: C1.2, C2.2, J2.1, J3.1, J4.1, J5.1, J7.0, J7.8, M1.6
LINE_IN: J7.12, R1.1
dynamixel data: J2.3, J7.14
microphone output: J3.3, J7.6
neopixel input: J5.3, J7.13
photo sensor output: J4.3, J7.5

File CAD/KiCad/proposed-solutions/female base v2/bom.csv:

Reference,Value,Footprint,Description
J4,photosensor,Body:J4_original,Original harness pin order retained. J6 now carries the local amplifier output.
J2,dxl mirror,Body:J2_original,Original harness pin order retained. J6 now carries the local amplifier output.
J7,DA15_Plug_MountingHoles,Body:J7_original,Original harness pin order retained. J6 now carries the local amplifier output.
J3,microphone,Body:J3_original,Original harness pin order retained. J6 now carries the local amplifier output.
J5,neopixel,Body:J5_original,Original harness pin order retained. J6 now carries the local amplifier output.
J6,Speaker,Body:J6_original,Original harness pin order retained. J6 now carries the local amplifier output.
R1,22K,Resistor_SMD:R_0603_1608Metric,
R2,3K3,Resistor_SMD:R_0603_1608Metric,
C1,220uF 10V / provisional,Capacitor_SMD:CP_Elec_6.3x5.8,"SMD polarized aluminium electrolytic, 6.3x5.8mm; pin 1 positive. Provisional local reservoir; verify actual amplifier transients and rail sag before release."
C2,100nF,Capacitor_SMD:C_0603_1608Metric,
M1,GF1002 / 1x11 female socket,Body:GF1002_PlugIn_1x11,"Plug-in module: 1x3, 1x2 and 1x4 downward male headers in an 11-pin female socket. Nominal underside gap 11mm. Pin 10=ROUT+, 11=ROUT- is provisional: verify module polarity before ordering."

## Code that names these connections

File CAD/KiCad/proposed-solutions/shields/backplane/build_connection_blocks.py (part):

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    frame('ARDUINO MEGA / TEENSY ADAPTER',89,20,185,104)
    p=parts['A1'];inputs=[pin for pin,n in p['pins'].items() if n and (pin.startswith('A') or '/mic direct' in n)]
    outputs=[pin for pin,n in p['pins'].items() if n and pin not in inputs and not pin.startswith(('GND','5V'))]
    power=[pin for pin,n in p['pins'].items() if n in ('GND','MEGA_5V')];unused=[pin for pin,n in p['pins'].items() if n is None]
    pins=[]
    for group,x,angle in [(inputs,101,0),(outputs,173,180)]:pins.extend((pin,x,61+2*i-(len(group)-1),angle) for i,pin in enumerate(group))
    pins.extend((pin,137+2*i-(len(power)-1),99,90) for i,pin in enumerate(power))
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    for i,ch in enumerate(['FEMALE 1','FEMALE 2','FEMALE 3','MALE 1','MALE 2'],1):
        x=66+(i-1)*34;text(ch,x-12,237,2,True);ref='JV'+str(i)
        pins=[('1',x-14,252,0),('2',x-14,258,0),('3',x+14,252,180),('4',x+14,258,180),('5',x,241,270)]
        unit(ref,(x,251),pins,(12,8));parts[ref]['pin_names'].update({'1':'TONE','2':'GND','3':'AUDIO OUT','4':'AGND','5':'+5V'})
        text(ref,x-4,246,1.7,True);passive('RLT'+str(i),x-6,270);led('DT'+str(i),x+6,270)
        passive('RL'+str(i),x-7,283,True);passive('R'+str([303,403,503,103,203][i-1]),x+5,282)
        passive('JP'+str([4,5,6,2,3][i-1]),x+5,296);unit('HV'+str(i),(x-7,297),[],(1,1),'hole')
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            escape=point[0]+2*dx,point[1]+2*dy
            assert escape not in obstacles,(net,point,escape)
            router.line(net,point,escape)
    spines={'GND':8,'AGND':12,'+5V':274,'MEGA_5V':278,'+12V':282}
    text('AGND = ANALOG RETURN | MEGA_5V = CONTROLLER 5 V | Dots join wires; crossings without dots stay separate.',12,437,1.65)
    if not reuse:
        for net,x in spines.items():router.line(net,(x,24),(x,424))
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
